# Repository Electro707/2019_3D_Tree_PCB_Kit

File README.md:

# 2019_3D_Tree_PCB_Kit
A soldering kit of a "3D" Christmas Tree

This repository is archived, as it's a one-time design.
Now files are hosted on Google Drive.

Link to website, in which the Google Drive link can be found:
[Link](https://electro707.com/documentation/PCB/2019_3DChristmasTree/index.php)

I may create a new general reposity for the kit that will be updated as time goes on 
(there also won't be any of the University of New Haven logos on that one).

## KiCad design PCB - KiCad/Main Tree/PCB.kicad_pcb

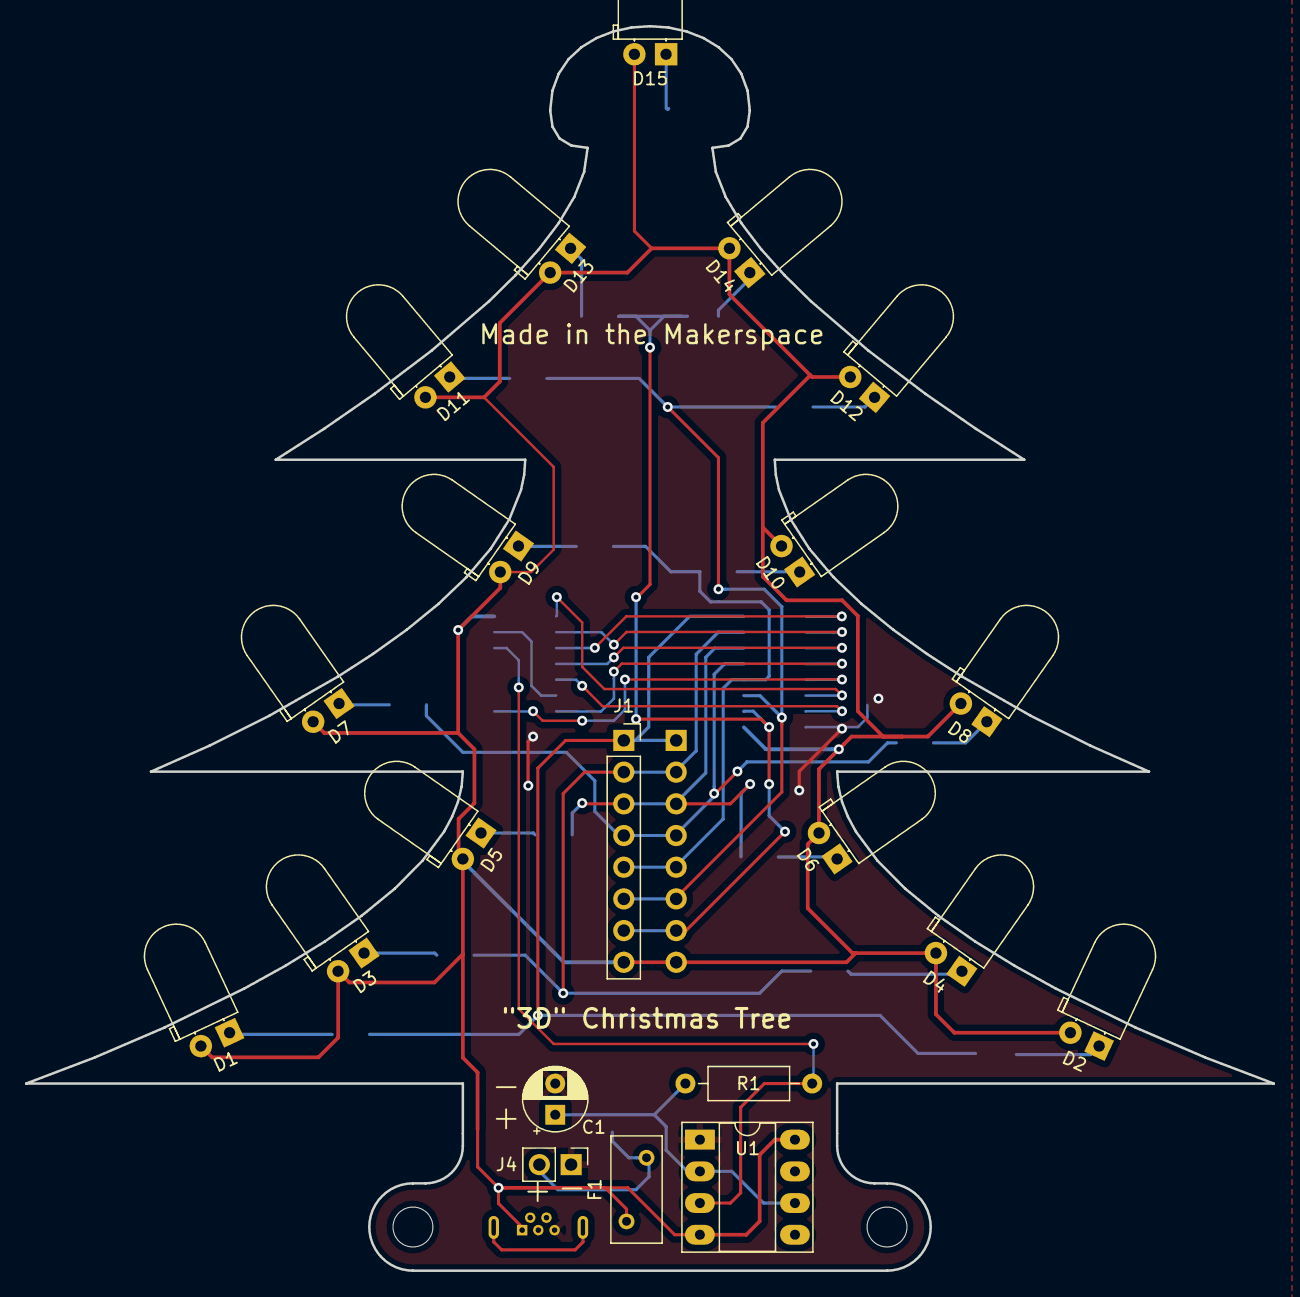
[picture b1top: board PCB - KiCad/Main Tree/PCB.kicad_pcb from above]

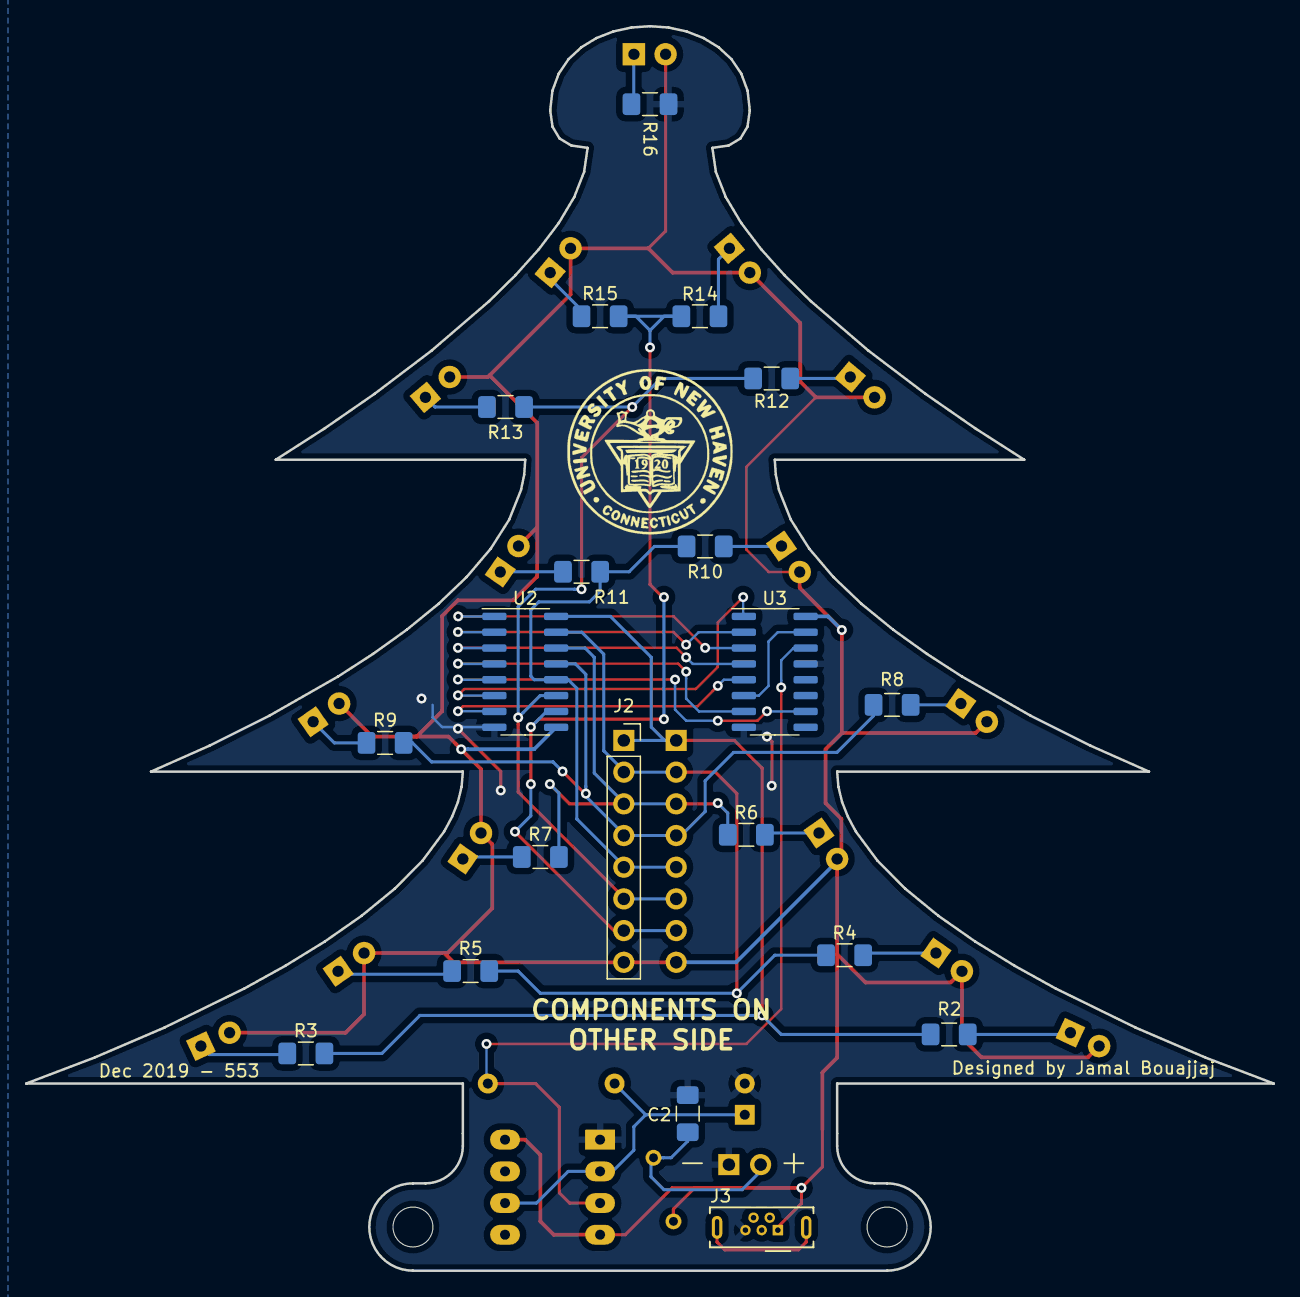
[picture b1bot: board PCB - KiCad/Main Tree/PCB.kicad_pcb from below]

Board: 2 copper layers, 100.0 x 99.8 mm, 43 parts (20 on the bottom side), 35 nets.

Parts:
C1: C; CP_Radial_D5.0mm_P2.50mm
C2: C; C_1206_3216Metric_Pad1.42x1.75mm_HandSolder
D1, D2, D3, D4, D5, D6, D7, D8, D9, D10, D11, D12, D13, D14, D15: LED_ALT; LED_D5.0mm_Horizontal_O1.27mm_Z3.0mm
F1: Polyfuse; Fuse_BelFuse_0ZRE0005FF_L8.3mm_W3.8mm
H1, H2: M3 hole; MountingHole_3.2mm_M3_DIN965
J1: Secondary Tree 1; PinSocket_1x08_P2.54mm_Vertical
J2: Secondary Tree 2; PinSocket_1x08_P2.54mm_Vertical
J3: USB_B_Micro; USB_Micro-B_Wuerth_614105150721_Vertical
J4: BATT; PinHeader_1x02_P2.54mm_Vertical
R1: R; R_Axial_DIN0207_L6.3mm_D2.5mm_P10.16mm_Horizontal
R2, R3, R4, R5, R6, R7, R8, R9, R10, R11, R12, R13, R14, R15, R16: 330; R_1206_3216Metric_Pad1.42x1.75mm_HandSolder
U1: LM555; DIP-8_W7.62mm_Socket_LongPads
U2: ULN2003; SOIC-16_3.9x9.9mm_P1.27mm
U3: 4017; SOIC-16_3.9x9.9mm_P1.27mm

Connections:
GND: C1.2, C2.2, J3.5, J4.1, R16.2, U1.1, U2.8, U3.8, U3.13
unnamed: C1.1, R1.2, U1.2, U1.6
unnamed: C2.1, F1.2, J4.2
unnamed: D1.1, R2.1
unnamed: D2.1, R3.1
unnamed: D3.1, R4.1
unnamed: D4.1, R5.1
unnamed: D5.1, R6.1
unnamed: D6.1, R7.1
unnamed: D7.1, R8.1
unnamed: D8.1, R9.1
unnamed: D9.1, R10.1
unnamed: D10.1, R11.1
unnamed: D11.1, R12.1
unnamed: D12.1, R13.1
unnamed: D13.1, R14.1
unnamed: D14.1, R15.1
unnamed: D15.1, R16.1
unnamed: J1.1, J2.1, R2.2, R3.2, U2.16
unnamed: J1.2, J2.2, R4.2, R5.2, U2.15
unnamed: J1.3, J2.3, R6.2, R7.2, U2.14
unnamed: J1.4, J2.4, R8.2, R9.2, U2.13
unnamed: J1.5, J2.5, R10.2, R11.2, U2.12
unnamed: J1.6, J2.6, R12.2, R13.2, U2.11
unnamed: J1.7, J2.7, R14.2, R15.2, U2.10
unnamed: R1.1, U1.3, U3.14
unnamed: U2.1, U3.3
unnamed: U2.2, U3.2
unnamed: U2.3, U3.4
unnamed: U2.4, U3.7
unnamed: U2.5, U3.10
unnamed: U2.6, U3.1
unnamed: U2.7, U3.5
unnamed: U3.6, U3.15
VCC: D1.2, D2.2, D3.2, D4.2, D5.2, D6.2, D7.2, D8.2, D9.2, D10.2, D11.2, D12.2, D13.2, D14.2, D15.2, F1.1, J1.8, J2.8, J3.1, U1.4, U1.8, U2.9, U3.16

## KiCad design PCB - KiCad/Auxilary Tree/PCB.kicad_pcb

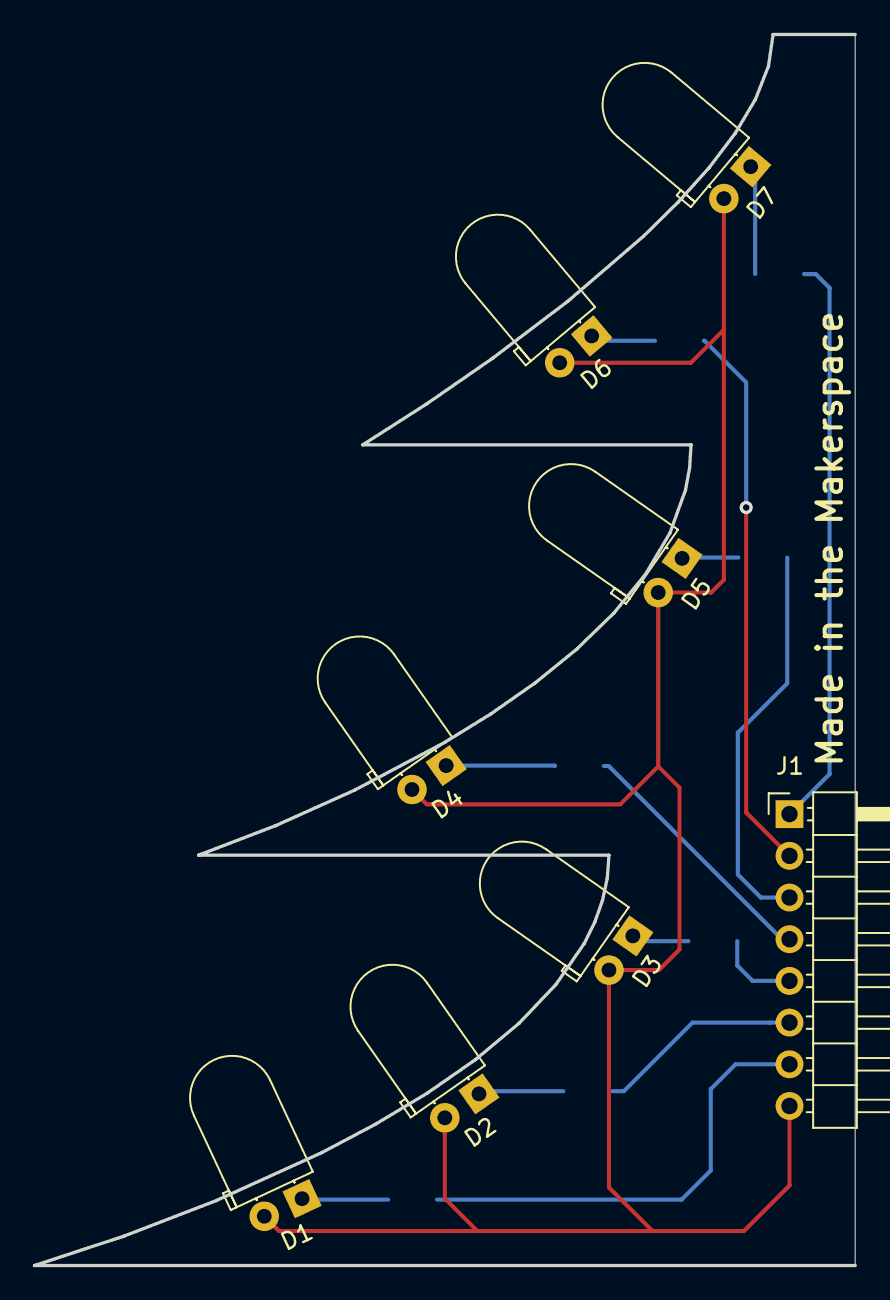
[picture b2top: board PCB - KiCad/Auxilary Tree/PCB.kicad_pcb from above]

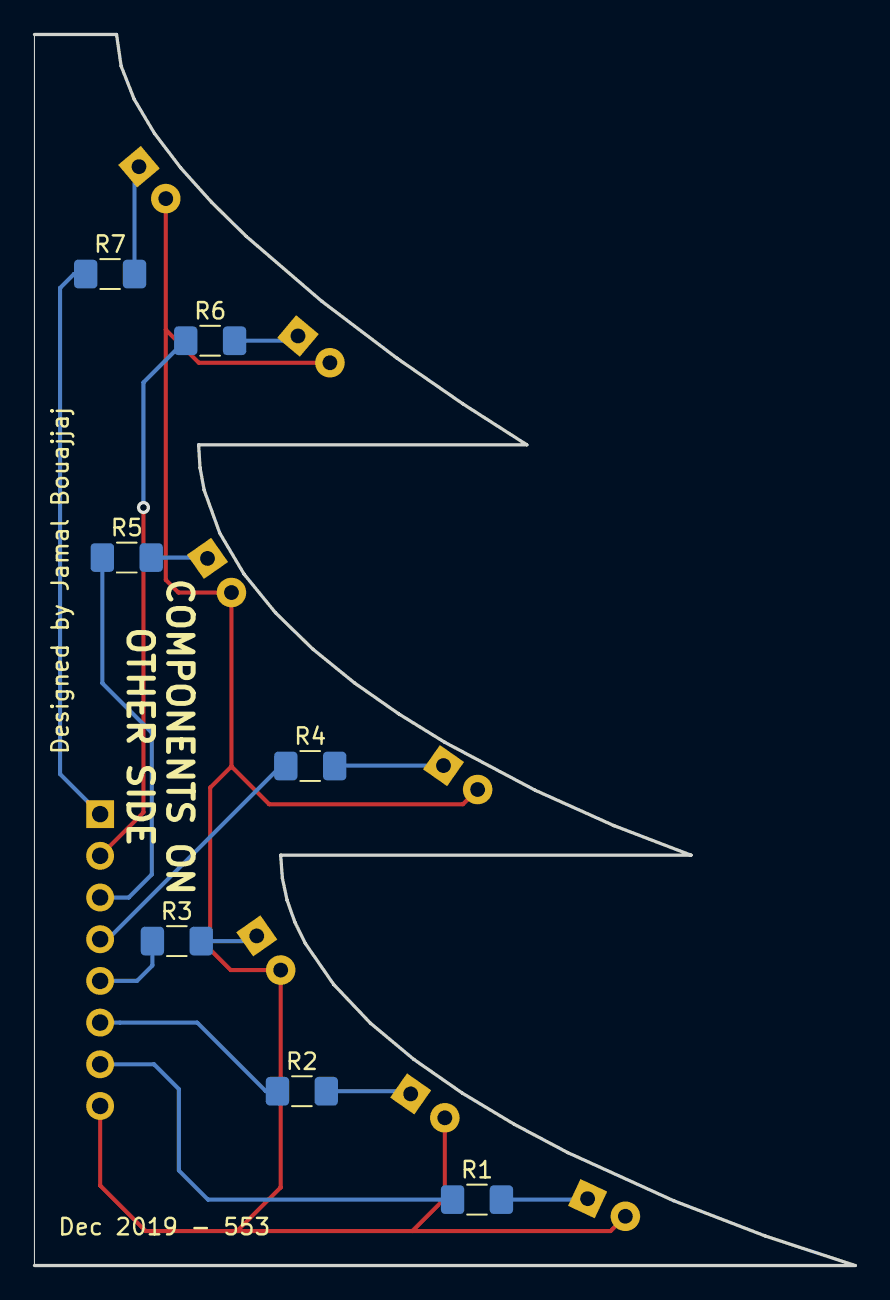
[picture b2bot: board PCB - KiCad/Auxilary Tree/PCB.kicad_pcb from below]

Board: 2 copper layers, 50.0 x 75.0 mm, 15 parts (7 on the bottom side), 15 nets.

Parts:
D1, D2, D3, D4, D5, D6, D7: LED_ALT; LED_D5.0mm_Horizontal_O1.27mm_Z3.0mm
J1: Conn_01x08; PinHeader_1x08_P2.54mm_Horizontal
R1, R2, R3, R4, R5, R6, R7: R; R_1206_3216Metric_Pad1.42x1.75mm_HandSolder

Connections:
unnamed: D1.1, R1.2
unnamed: D1.2, D2.2, D3.2, D4.2, D5.2, D6.2, D7.2, J1.8
unnamed: D2.1, R2.2
unnamed: D3.1, R3.2
unnamed: D4.1, R4.2
unnamed: D5.1, R5.2
unnamed: D6.1, R6.2
unnamed: D7.1, R7.2
unnamed: J1.1, R7.1
unnamed: J1.2, R6.1
unnamed: J1.3, R5.1
unnamed: J1.4, R4.1
unnamed: J1.5, R3.1
unnamed: J1.6, R2.1
unnamed: J1.7, R1.1

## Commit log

2019-12-22 Some drawing and part changes
2020-04-16 Pre-Archive Change
